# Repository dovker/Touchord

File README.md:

# Touchord

Touchord is an open source chord-generating MIDI controller featuring a touch bar interface. It is designed for musicians seeking versatile chordal playing and performance options and for makers looking for a highly modifyable product with a realistic and fun use.

## [TOUCHORD DIY KIT PRE-ORDERS](https://daugdara.com/products/touchord-diy-kit)

## Motivation

Making music without formal training is hard. Learning theory takes time, and when the goal is to create and express ideas quickly, it can feel tedious. Chord progressions and harmony are crucial yet difficult to master; exploring by ear works, but entering complex chords on guitar or piano is slow. That is where chord‑generating synths and MIDI controllers help.

**Why not buy an existing similar device?** Many are closed‑source and built by unestablished companies with limited support histories. When projects are abandoned or parts become unavailable, devices turn into e‑waste.

Touchord addresses these problems. Components are common, 3D‑printable, or manufacturable at a reasonable cost, thus repairs and replacements remain feasible. Open development also streamlines bug fixes and issue tracking because contributors can help accelerate software improvements. And if we for some reason stop developing new updates or cannot contribute anymore, community still remains along with the source code and all the production files, keeping the project alive.

## Licensing and Legal Notice

**Copyright © 2026 MB Daugdara. All rights reserved.**

**Trademarks:**
- Touchord™ is a trademark of MB Daugdara
- Touchord™ logo is a trademark of MB Daugdara

**Intellectual Property:**
- The Touchord name and logo are the exclusive property of MB Daugdara
- Firmware is licensed under GNU General Public License v3.0
- The 3D model design files and PCB Files are licensed under CERN-OHL-S-2.0
- The license does not grant rights to use the company name or logo

**Restrictions:**
- You may not use the company name or logo to endorse derivative commercial works
- You must include this notice when distributing modified versions
- See LICENSE file for full CERN-OHL-S-2.0 terms

## Features

- **Three Operating Modes:**
  - **Strum Mode:** Harp style playing for plucked synths.
  - **Omni Mode:** An omni-chord style play mode mimicking the strumming of an omnichord.
  - **Composer Mode:** Allows adjustment of chord qualities directly via the touch bar for chord customization.
  - **Perform Mode:** Uses the touch bar’s pressure sensitivity for expressive live performances.
  - **Drum Mode:** A simple mode with chromatically mapped keys and the touch bar controlling velocity.

- **Chord Layout:**
  - Each key corresponds to a chord degree in a musical key.
  - Supports custom musical keys and customizable chords on each key.

- **Hardware:**
  - Uses the RP2350 microcontroller chip.
  - Programmed with the PicoSDK in C.
  - Cherry MX style mechanical switches.
  - 6 control buttons.
  - 7 chord keys sized 3u, equipped with 3u plate-mounted stabilizers for enhanced stability.
  - Touch bar: [Trill Bar by Bella](https://bela.io/products/trill/) ([GitHub](https://github.com/BelaPlatform/Trill)) providing multi-touch and pressure sensing.
  - Display: Standard 0.96" 128x64 OLED SSD1306 screen.

- **Enclosure:**
  - Combination of 3D printed carbon fiber reinforced PETG base and CNC machined aluminum top.
  - Optionally, the top can also be fabricated via 3D printing.

- **Connectivity:**
  - USB Type-C MIDI support.
  - TRS MIDI support (User switchable in software):
    - **TRS Type A (Standard MIDI TRS)**
    - **TRS Type B (Roland TRS MIDI)**

---

## Contribution

Check `CONTRIBUTING.md` for more info.

### AI Usage

AI usage on Bug Fixes and Code Auditing is welcome, if done with proper testing, cleanup and no blind trust. Please disclose AI usage in Pull Requests.
Features are better left for humans to write.

---

## Showcase

## User Showcase

## Projects based on Touchord

### "Ghetto" Touchord made using Pico 2W by [nlpeeee](https://github.com/nlpeeee/TCw)

## Special Thanks

I wanted to share my experience with [PCBWay](https://www.pcbway.com/), as I used it for prototyping and although they have helped me produce one of the batches at their cost, this opinion is my own. My choice to go with PCB Way was first, and only then did I ask for their help.

They have been an amazing experience, especially comparing to their biggest competitors, as for the same price I was able to manufacture boards of way better quality. I couldn't have made this project without PCBA services, as soldering small footprint components are too time consuming and expensive to setup.

What I have found is that the quality of thru-holes, soldering are way better and feel like an actual professional product instead of a draft board. Also, the fact that components can be sourced from anywhere, it doesn't have to be a specific selection of components and other components costing more than a standard price, unlike their competitors. Also, their care of the customer surprised me as I was asked multiple times, whether the components I chose are the right ones (There have been issues with the BOM), and one of the more suprising questions I got was whether the color of soldermask could be changes, as properties of black soldermask wouldn'tve played well with my design. That was amazing, as other service providers just apply blind trust and manufacture the board.

Overall, an amazing experience, especially for anyone looking to prototype PCB's that don't feel like toys, guaranteeing that what you designed will be what you get.

---

*Find the Trill Bar by Bella:* [https://bela.io/products/trill/](https://bela.io/products/trill/)
*Trill Bar GitHub repository:* [https://github.com/bela-platform/trill](https://github.com/BelaPlatform/Trill)

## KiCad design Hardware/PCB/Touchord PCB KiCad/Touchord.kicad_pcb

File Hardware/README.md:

## Licensing and Legal Notice

**Copyright © 2026 MB Daugdara. All rights reserved.**

**Trademarks:**
- Touchord™ is a trademark of MB Daugdara
- Touchord™ logo is a trademark of MB Daugdara

**Intellectual Property:**
- The Touchord name and logo are the exclusive property of MB Daugdara
- Firmware is licensed under GNU General Public License v3.0
- The 3D model design files are licensed under CERN-OHL-S-2.0
- The license does not grant rights to use the company name or logo

**Restrictions:**
- You may not use the company name or logo to endorse derivative commercial works
- You must include this notice when distributing modified versions
- See LICENSE file for full CERN-OHL-S-2.0 terms

# 3D Models

Parametric 3D Models are stored in Enclosure/Parametric folder, containing Fusion 360 Files. 
For those, who prefer not to use Fusion360, parametric models are modifiable in [Makerworld](https://makerworld.com/en/models/2870548-touchord-open-source-midi-controller-shell)

For 3D Printing and custom tolerances Models can be downloaded in [Makerworld](https://makerworld.com/en/models/2870548-touchord-open-source-midi-controller-shell)

STEP Files are in Enclosure folder.

When 3D Printing, adjust tolerances and screw hole sizes accordingly. Recommended orientations:
- Base, flat side on the build plate;
- Top shell, top flat part on the build plate, tree supports (Requires extra removal);
- Keycaps, flat side on the bed;
- Key plates, flat on the bed.

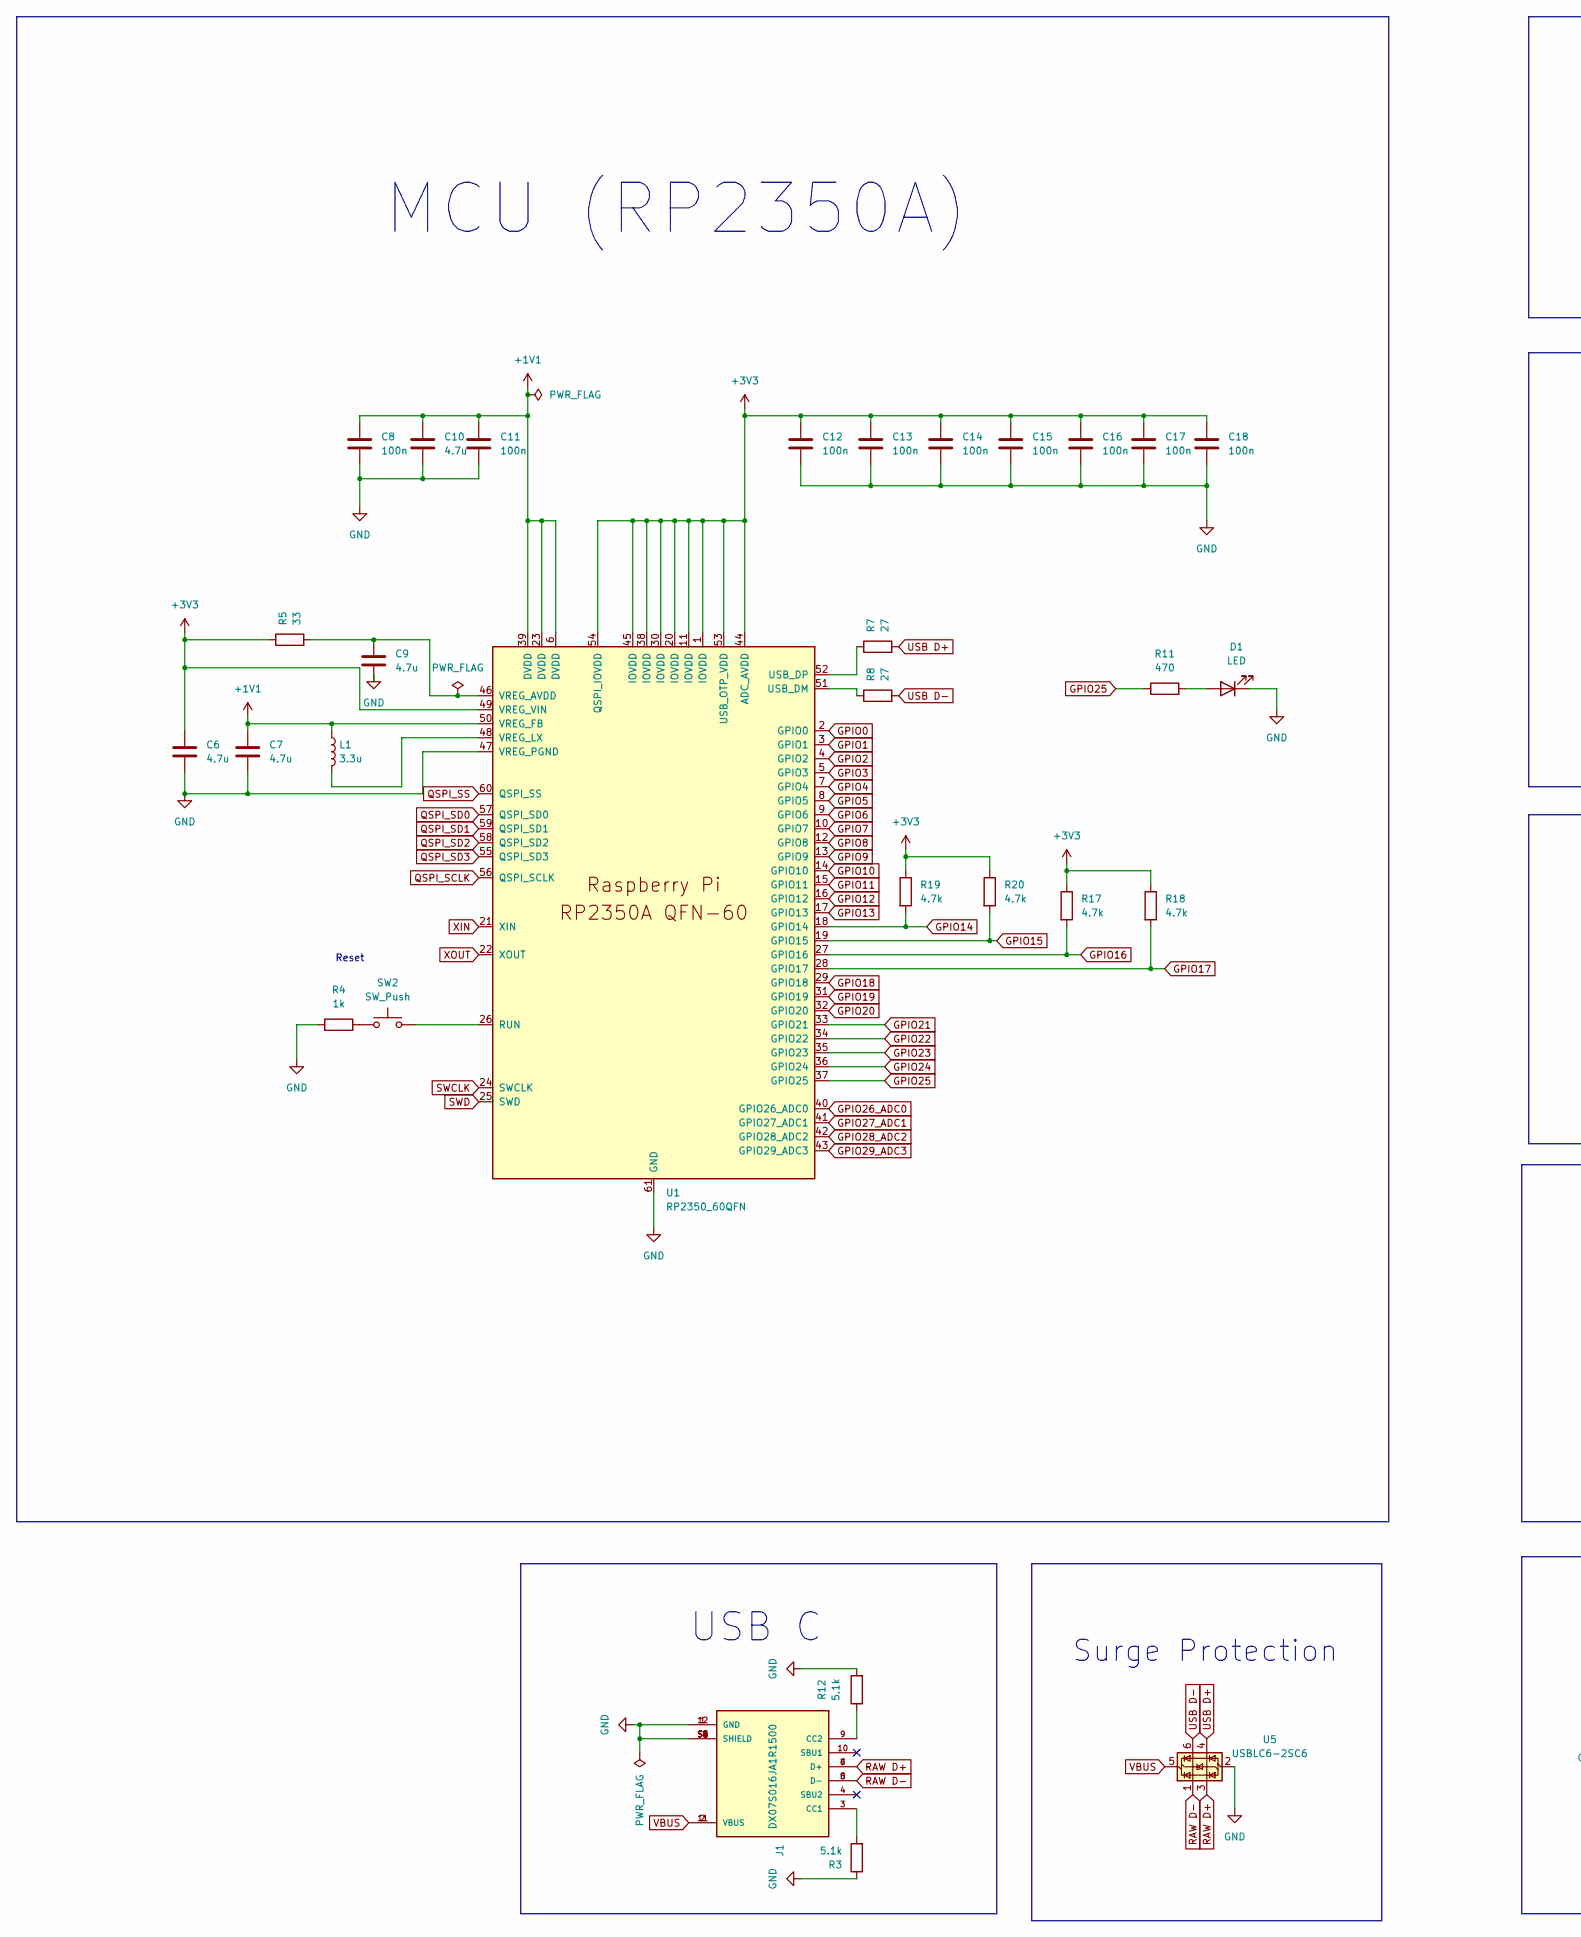
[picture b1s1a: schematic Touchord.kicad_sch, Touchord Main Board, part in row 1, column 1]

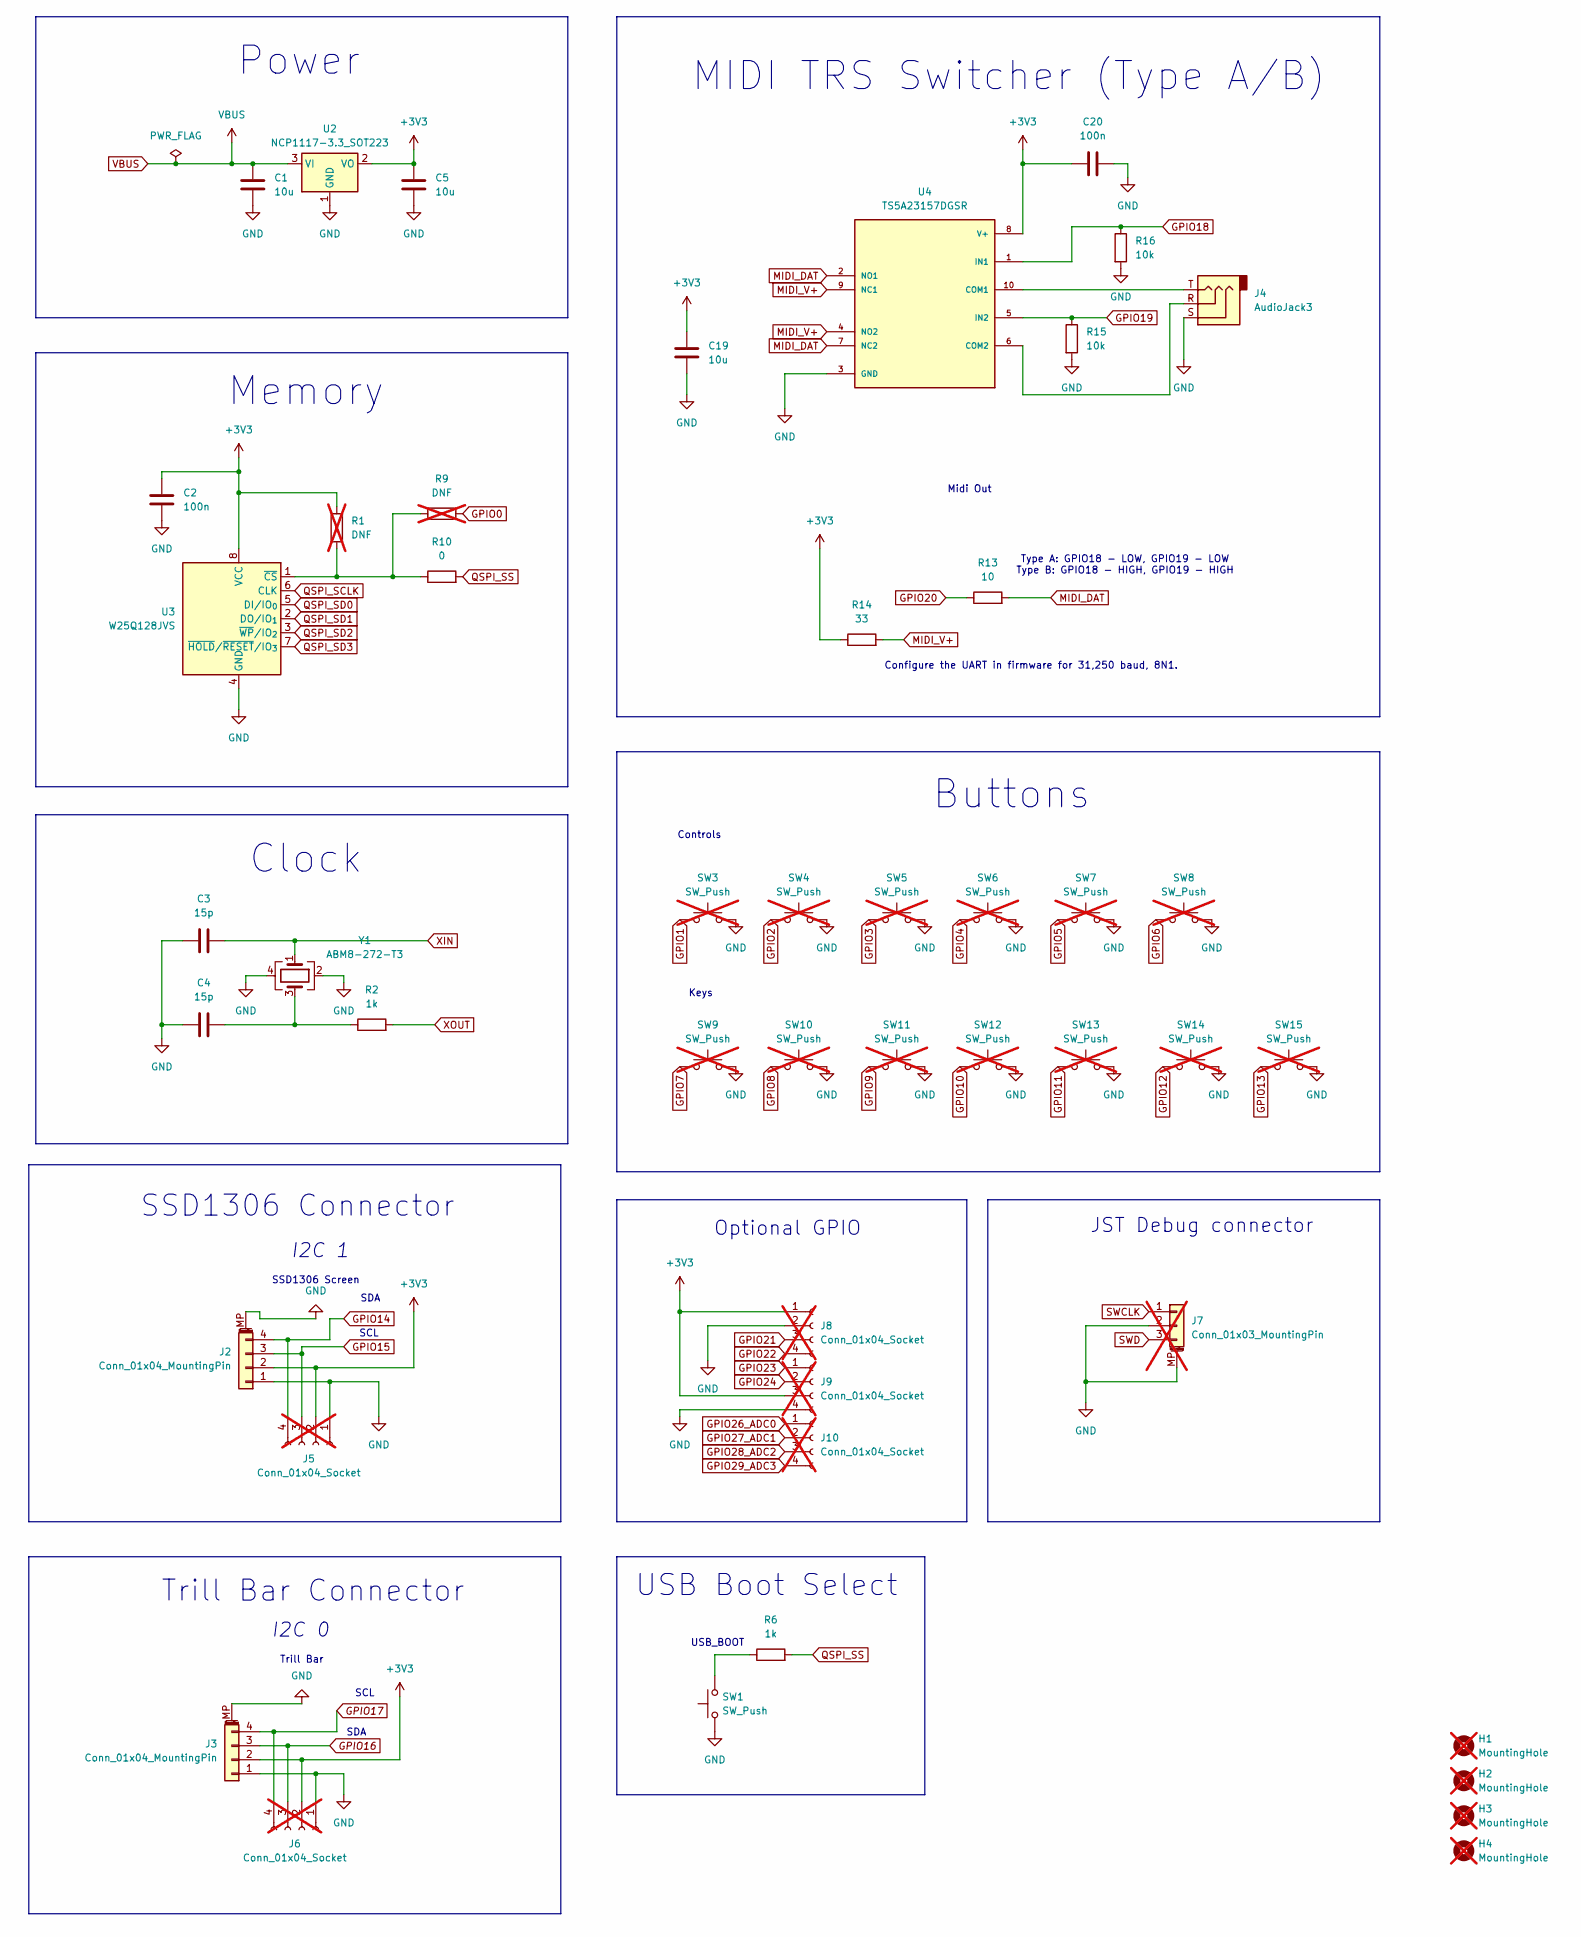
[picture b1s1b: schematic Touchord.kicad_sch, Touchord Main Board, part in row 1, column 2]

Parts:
C1, C5, C19: 10u; C_0805_2012Metric
C2, C8, C11, C12, C13, C14, C15, C16, C17, C18, C20: 100n; C_0402_1005Metric
C3, C4: 15p; C_0402_1005Metric
C6, C7: 4.7u; C_0402_1005Metric_small_pads
C9, C10: 4.7u; C_0402_1005Metric
D1: LED; LED_0603_1608Metric
H1, H2, H3, H4: MountingHole; MountingHole_2.7mm_M2.5; not fitted
J1: DX07S016JA1R1500; JAE_DX07S016JA1R1500; PARTREV 1
J2, J3: Conn_01x04_MountingPin; JST_SH_SM04B-SRSS-TB_1x04-1MP_P1.00mm_Horizontal
J4: AudioJack3; Jack_3.5mm_CUI_SJ-3523-SMT_Horizontal
J5, J6, J8, J9, J10: Conn_01x04_Socket; SolderWire-0.75sqmm_1x04_P4.8mm_D1.25mm_OD2.3mm; not fitted
J7: Conn_01x03_MountingPin; JST_SH_SM03B-SRSS-TB_1x03-1MP_P1.00mm_Horizontal; not fitted
L1: 3.3u; L_pol_2016
R1, R9: DNF; R_0402_1005Metric; not fitted
R2, R4, R6: 1k; R_0402_1005Metric
R3, R12: 5.1k; R_0402_1005Metric
R5, R14: 33; R_0402_1005Metric
R7, R8: 27; R_0402_1005Metric
R10: 0; R_0402_1005Metric
R11: 470; R_0402_1005Metric
R13: 10; R_0402_1005Metric
R15, R16: 10k; R_0402_1005Metric
R17, R18, R19, R20: 4.7k; R_0402_1005Metric
SW1, SW2: SW_Push; SW_TS-1088-AR02016
SW3, SW4, SW5, SW6, SW7, SW8: SW_Push; SW_Cherry_MX_PCB_1.00u; not fitted
SW9, SW10, SW11, SW12, SW13, SW14, SW15: SW_Push; SW_Cherry_MX_PCB_3.00u_90deg; not fitted
U1: RP2350_60QFN; RP2350-QFN-60-1EP_7x7_P0.4mm_EP3.4x3.4mm_ThermalVias
U2: NCP1117-3.3_SOT223; SOT-223-3_TabPin2
U3: W25Q128JVS; SOIC-8_5.3x5.3mm_P1.27mm
U4: TS5A23157DGSR; SOP50P490X110-10N; PARTREV F
U5: USBLC6-2SC6; SOT-23-6
Y1: ABM8-272-T3; Crystal_SMD_3225-4Pin_3.2x2.5mm

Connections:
+1V1: C7.1, C8.1, C10.1, C11.1, L1.1, U1.6 (DVDD), U1.23 (DVDD), U1.39 (DVDD), U1.50 (VREG_FB)
+3V3: C2.1, C5.1, C6.1, C12.1, C13.1, C14.1, C15.1, C16.1, C17.1, C18.1, C19.1, C20.1, J2.2, J3.2, J5.2, J6.2, J8.1, J9.3, R1.1, R5.1, R14.1, R17.1, R18.1, R19.1, R20.1, U1.1 (IOVDD), U1.11 (IOVDD), U1.20 (IOVDD), U1.30 (IOVDD), U1.38 (IOVDD), U1.44 (ADC_AVDD), U1.45 (IOVDD), U1.49 (VREG_VIN), U1.53 (USB_OTP_VDD), U1.54 (QSPI_IOVDD), U2.2 (VO), U3.8 (VCC), U4.8 (V+)
GND: C1.2, C2.2, C3.1, C4.1, C5.2, C6.2, C7.2, C8.2, C9.2, C10.2, C11.2, C12.2, C13.2, C14.2, C15.2, C16.2, C17.2, C18.2, C19.2, C20.2, D1.1 (K), J1.1 (GND), J1.12 (GND), J1.S1 (SHIELD), J1.S2 (SHIELD), J1.S3 (SHIELD), J1.S4 (SHIELD), J1.S5 (SHIELD), J1.S6 (SHIELD), J2.1, J2.MP (MountPin), J3.1, J3.MP (MountPin), J4.S, J5.1, J6.1, J7.2, J7.MP (MountPin), J8.2, J9.4, R3.1, R4.1, R12.2, R15.2, R16.2, SW1.1, SW3.2, SW4.2, SW5.2, SW6.2, SW7.2, SW8.2, SW9.2, SW10.2, SW11.2, SW12.2, SW13.2, SW14.2, SW15.2, U1.47 (VREG_PGND), U1.61 (GND), U2.1 (GND), U3.4 (GND), U4.3 (GND), U5.2 (GND), Y1.2, Y1.4
GPIO0: R9.1, U1.2 (GPIO0)
GPIO1: SW3.1, U1.3 (GPIO1)
GPIO2: SW4.1, U1.4 (GPIO2)
GPIO3: SW5.1, U1.5 (GPIO3)
GPIO4: SW6.1, U1.7 (GPIO4)
GPIO5: SW7.1, U1.8 (GPIO5)
GPIO6: SW8.1, U1.9 (GPIO6)
GPIO7: SW9.1, U1.10 (GPIO7)
GPIO8: SW10.1, U1.12 (GPIO8)
GPIO9: SW11.1, U1.13 (GPIO9)
GPIO10: SW12.1, U1.14 (GPIO10)
GPIO11: SW13.1, U1.15 (GPIO11)
GPIO12: SW14.1, U1.16 (GPIO12)
GPIO13: SW15.1, U1.17 (GPIO13)
GPIO14: J2.4, J5.4, R19.2, U1.18 (GPIO14)
GPIO15: J2.3, J5.3, R20.2, U1.19 (GPIO15)
GPIO16: J3.3, J6.3, R17.2, U1.27 (GPIO16)
GPIO17: J3.4, J6.4, R18.2, U1.28 (GPIO17)
GPIO18: R16.1, U1.29 (GPIO18), U4.1 (IN1)
GPIO19: R15.1, U1.31 (GPIO19), U4.5 (IN2)
GPIO20: R13.1, U1.32 (GPIO20)
GPIO21: J8.3, U1.33 (GPIO21)
GPIO22: J8.4, U1.34 (GPIO22)
GPIO23: J9.1, U1.35 (GPIO23)
GPIO24: J9.2, U1.36 (GPIO24)
GPIO25: R11.1, U1.37 (GPIO25)
GPIO26_ADC0: J10.1, U1.40 (GPIO26_ADC0)
GPIO27_ADC1: J10.2, U1.41 (GPIO27_ADC1)
GPIO28_ADC2: J10.3, U1.42 (GPIO28_ADC2)
GPIO29_ADC3: J10.4, U1.43 (GPIO29_ADC3)
MIDI_DAT: R13.2, U4.2 (NO1), U4.7 (NC2)
MIDI_V+: R14.2, U4.4 (NO2), U4.9 (NC1)
unnamed: C4.2, R2.1, Y1.3
unnamed: D1.2 (A), R11.2
unnamed: J1.3 (CC1), R3.2
unnamed: J1.9 (CC2), R12.1
unnamed: R4.2, SW2.1
unnamed: R6.1, SW1.2
unnamed: SW2.2, U1.26 (RUN)
unnamed: R8.1, U1.51 (USB_DM)
unnamed: R7.1, U1.52 (USB_DP)
unnamed: C9.1, R5.2, U1.46 (VREG_AVDD)
unnamed: L1.2, U1.48 (VREG_LX)
unnamed: R1.2, R9.2, R10.1, U3.1 (~CS)
unnamed: J4.T, U4.10 (COM1)
unnamed: J4.R, U4.6 (COM2)
QSPI_SCLK: U1.56 (QSPI_SCLK), U3.6 (CLK)
QSPI_SD0: U1.57 (QSPI_SD0), U3.5 (DI/IO_{0})
QSPI_SD1: U1.59 (QSPI_SD1), U3.2 (DO/IO_{1})
QSPI_SD2: U1.58 (QSPI_SD2), U3.3 (~WP/IO_{2})
QSPI_SD3: U1.55 (QSPI_SD3), U3.7 (~HOLD/~RESET/IO_{3})
QSPI_SS: R6.2, R10.2, U1.60 (QSPI_SS)
RAW D+: J1.6 (D+), J1.7 (D+), U5.3 (I/O2)
RAW D-: J1.5 (D-), J1.8 (D-), U5.1 (I/O1)
SWCLK: J7.1, U1.24 (SWCLK)
SWD: J7.3, U1.25 (SWD)
USB D+: R7.2, U5.4 (I/O2)
USB D-: R8.2, U5.6 (I/O1)
VBUS: C1.1, J1.2 (VBUS), J1.11 (VBUS), U2.3 (VI), U5.5 (VBUS)
XIN: C3.2, U1.21 (XIN), Y1.1
XOUT: R2.2, U1.22 (XOUT)

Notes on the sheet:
I2C 1
Controls
MCU (RP2350A)
Surge Protection
SSD1306 Connector
JST Debug connector
USB_BOOT
Midi Out
Keys
Type A: GPIO18 - LOW, GPIO19 - LOW Type B: GPIO18 - HIGH, GPIO19 - HIGH
SSD1306 Screen
MIDI TRS Switcher (Type A/B)
SCL
Memory
Trill Bar Connector
USB C
Trill Bar
I2C 0
Clock
SDA
Reset
Power
Buttons
Configure the UART in firmware for 31,250 baud, 8N1.
Optional GPIO
USB Boot Select

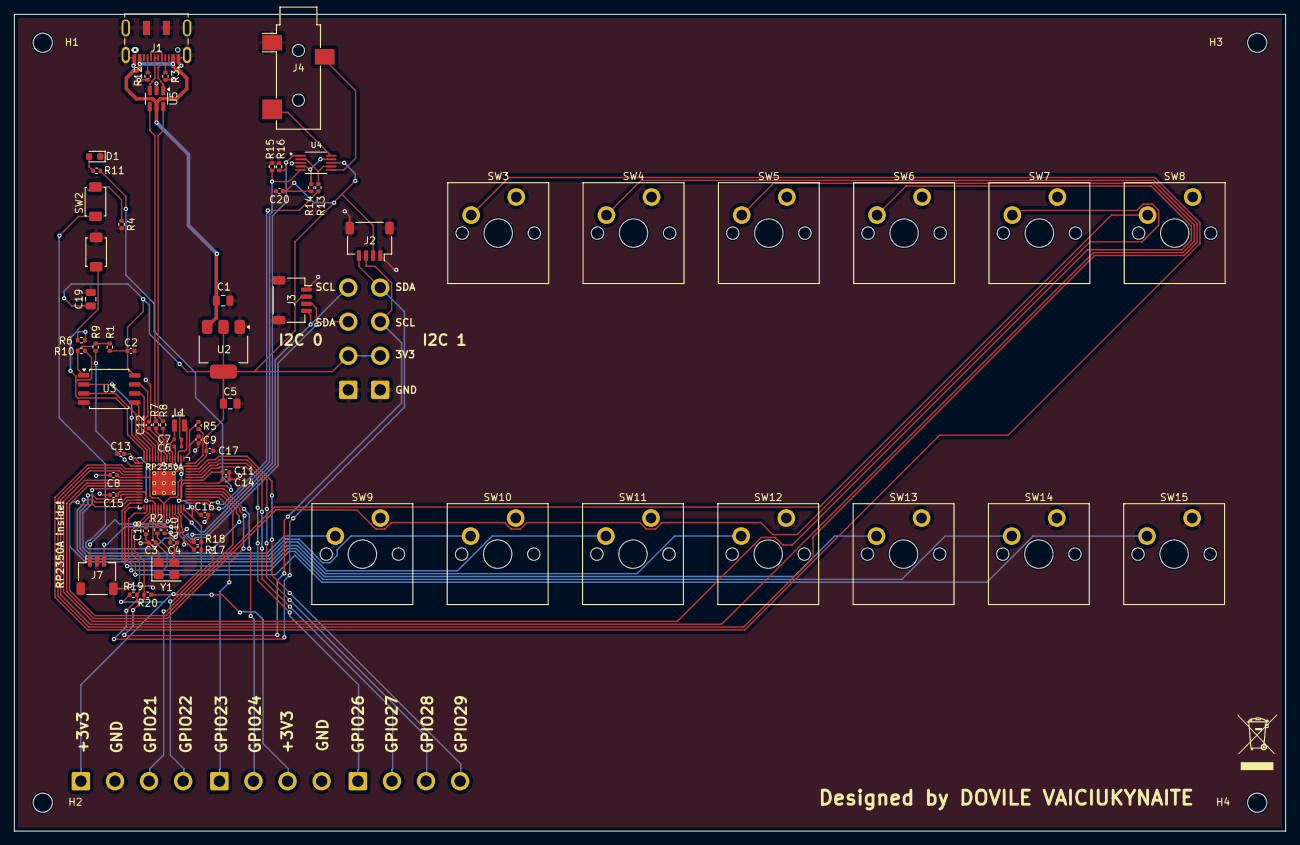
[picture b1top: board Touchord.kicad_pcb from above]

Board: 2 copper layers, 179.0 x 115.0 mm, 77 parts (0 on the bottom side), 64 nets.

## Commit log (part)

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2025-07-12 Midi Init
2025-07-12 Note API Rewrite
    UNTESTED
2025-08-05 TUSB Midi device, initial refactoring
2025-08-05 Added renders
2025-08-17 Imported Display driver, wrote a Trill bar driver
2025-08-28 Fixed trill driver precision errors
2025-08-28 Added Manual Bootsel
2025-08-30 cleanup
2025-09-07 Cleanup, Modularity, Working prototype
2025-09-07 Added Omni style
2025-09-14 General fixes, TRS MIDI support
2025-09-30 Fixed some bugs, added Web Settings Editor
2025-09-30 Updated Settings editor
2025-10-23 Added Schematic
2025-10-28 Create LICENSE
2025-11-09 Fixed Omni Mode
    Adjusted Omni mode to mimic Omnichord
2025-12-29 Photos added
2025-12-29 Added work-in-progress enclosures
2025-12-30 Added showcase image
2026-01-12 Design and layout PDF's
2026-01-14 Added drum mode, settings page
    TODO: Inversion mode display, saving, melody mode
2026-04-22 add built in synth
2026-04-22 Add pico rand shim for AMY build
2026-05-12 working for small breadboard
2026-05-13 add encoder test
2026-05-13 add optimization research findings
2026-05-13 AMY/I2S optimizations
2026-05-31 Added New Enclosures.
2026-05-31 Release v1.0.0
    First tagged release. Highlights:
    - Compose mode with Jazz substitutions, voice-leading, trill tooltip.
    - Drum mode with 7-pad grid.
    - Strum / Omni / Perform / Settings modes; transitions between all.
    - Persistent presets (8 slots), four custom scales, MIDI channel /
    velocity / TRS-type configuration.
